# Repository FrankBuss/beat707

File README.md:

# Development environment

## Programmer and debug connection

For programming you can use an USBasp. The red wire of the USBasp programmer needs to be connected to the `pin 1` location:

For debugging, there is the jumper J5 near the MIDI connector, to connect a 5V UART receiver. Connect the top pin to GND (black wire in the image) and the bottom pin to the UART RX input (grey wire) :

## Fuse programming

The Arduino IDE doesn't flash the ATmega fuses, so initially you need to do this from the command line with avrdude like this:

```
avrdude -cusbasp -p m328 -B 10 -U lfuse:w:0xff:m
```
The output should look like this:

```
avrdude: set SCK frequency to 93750 Hz
avrdude: AVR device initialized and ready to accept instructions

Reading | ################################################## | 100% 0.00s

avrdude: Device signature = 0x1e9514 (probably m328)
avrdude: reading input file "0xff"
avrdude: writing lfuse (1 bytes):

Writing | ################################################## | 100% 0.00s

avrdude: 1 bytes of lfuse written
avrdude: verifying lfuse memory against 0xff:
avrdude: load data lfuse data from input file 0xff:
avrdude: input file 0xff contains 1 bytes
avrdude: reading on-chip lfuse data:

Reading | ################################################## | 100% 0.00s

avrdude: verifying ...
avrdude: 1 bytes of lfuse verified

avrdude: safemode: Fuses OK (E:FF, H:D9, L:FF)

avrdude done.  Thank you.
```

## Arduino IDE setup

First install the Arduino IDE. It was tested with Arduino 1.8.13. Then add the URL https://mcudude.github.io/MiniCore/package_MCUdude_MiniCore_index.json to "File->Preferences->Settings->Additional Board Manager URLs". Then you can install the new board with "Tools->Board->Boards Manager". Install "MiniCore by MCUdude", tested with version 2.1.0.

For programming you need an USBasp. You need to reduce the clock speed in the file `/home/username/bin/arduino-1.8.9/hardware/arduino/avr/programmers.txt`, where `username` is your username (on Linux, on Windows and Mac it might be different, see [here](https://www.arduino.cc/en/hacking/preferences)). Search for the `usbasp.program.extra_params` line and add the parameter `-B 10`. The full line now looks like this:

```
usbasp.program.extra_params=-Pusb -B 10
```

Restart the Arduino IDE after changing it.

After restart, select the new board: Tools->Board->MiniCore->ATmega328. For flashing the firmware, configure the following settings (Board, Clock, Variant and Bootloader needs to be changed):

Then select your programmer, for example USBasp:

After this you can program the ATmega328 on the board from the Arduino IDE by clicking on the right arrow.

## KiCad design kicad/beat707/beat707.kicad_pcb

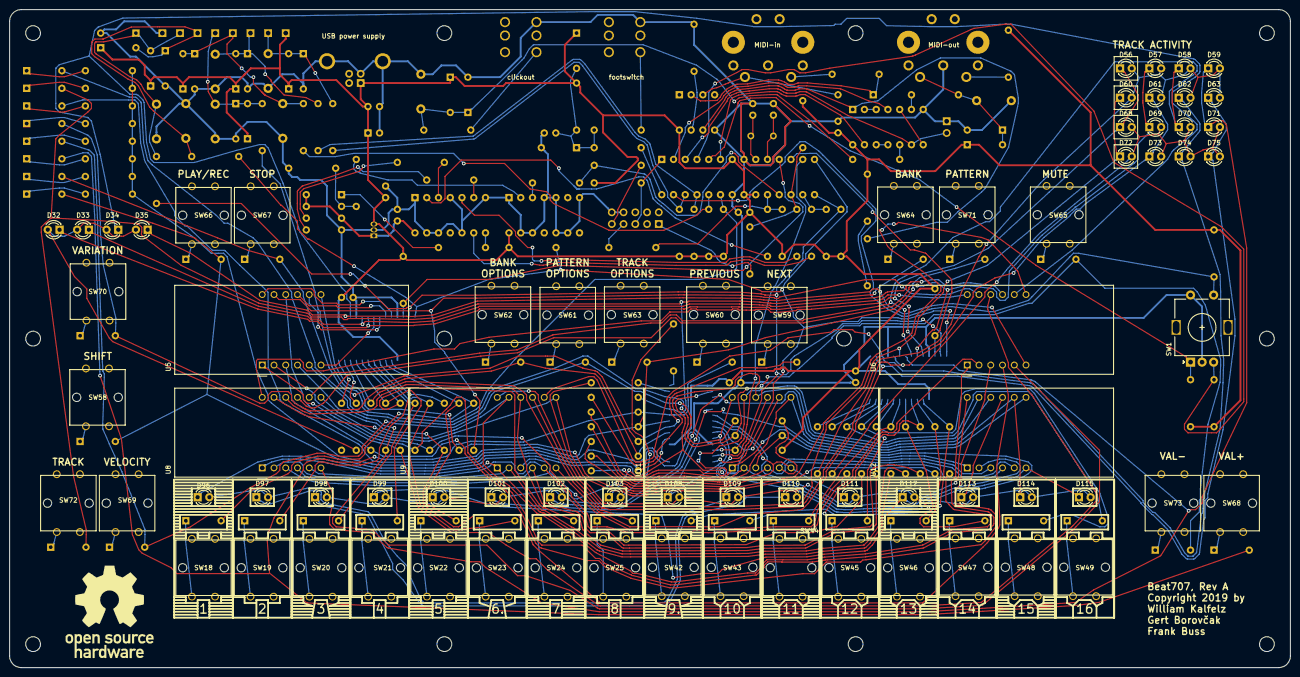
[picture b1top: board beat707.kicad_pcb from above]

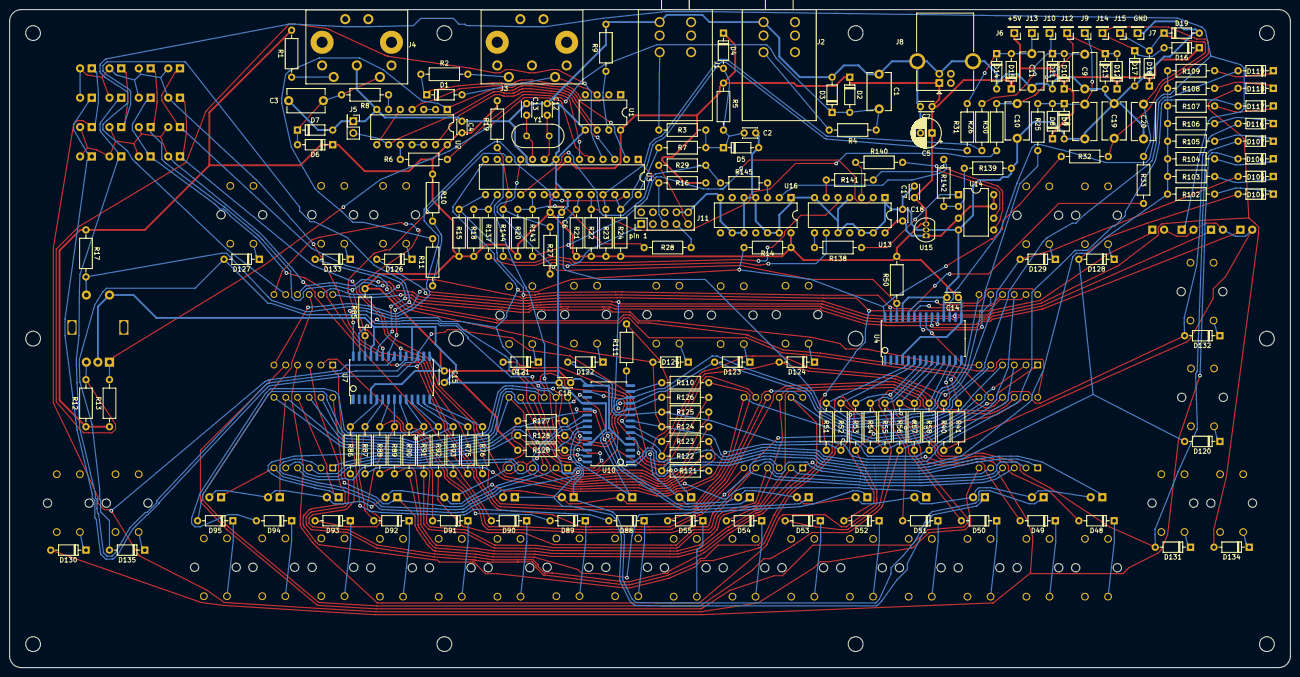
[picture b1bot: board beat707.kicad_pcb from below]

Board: 2 copper layers, 276.9 x 142.2 mm, 276 parts (188 on the bottom side), 188 nets.

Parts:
C1, C3, C8, C9, C10, C11, C19, C20: 1nF; C_Disc_D8.0mm_W5.0mm_P7.50mm
C2, C4, C6, C7, C14, C15, C16, C17, C18: 100nF; C_Disc_D3.0mm_W2.0mm_P2.50mm
C5: 47uF; CP_Radial_D6.3mm_P2.50mm
C12, C13: 22pF; C_Disc_D3.0mm_W2.0mm_P2.50mm
D1, D2, D3, D4, D5, D6, D7, D8, D9, D10, D11, D12, D13, D14, D15, D16, D17, D18, D19, D48, D49, D50, D51, D52, D53, D54, D55, D88, D89, D90, D91, D92, D93, D94, D95, D104, D105, D106, D107, D116, D117, D118, D119, D120, D121, D122, D123, D124, D125, D126, D127, D128, D129, D130, D131, D132, D133, D134, D135: 1N4148; D_DO-35_SOD27_P7.62mm_Horizontal
D32, D33, D34, D35, D56, D57, D58, D59, D60, D61, D62, D63, D68, D69, D70, D71, D72, D73, D74, D75, D96, D97, D98, D99, D100, D101, D102, D103, D108, D109, D110, D111, D112, D113, D114, D115: LED; LED_D3.0mm
H1, H2, H3, H4, H5, H6, H7, H8, H9, H10, H11, H12: MountingHole; MountingHole_3.2mm_M3
J1: footswitch; trs
J2: click-out; trs
J3: MIDI-in; din-5
J4: MIDI-out; din-5
J5: serial debug; PinHeader_2x01_P2.54mm_Vertical
J6: +5V; PinHeader_1x01_P2.54mm_Vertical
J7: GND; PinHeader_1x01_P2.54mm_Vertical
J8: USB_B; USB_B_OST_USB-B1HSxx_Horizontal
J9, J10, J12, J13, J14, J15: free IO; PinHeader_1x01_P2.54mm_Vertical
J11: ISP; PinHeader_2x05_P2.54mm_Vertical
LOGO1: Logo_Open_Hardware_Small; OSHW-Logo_19x20mm_SilkScreen
R1, R2, R3, R4, R6, R8, R10, R11, R25, R26, R30, R31, R32, R33, R40, R41, R75, R76, R110, R111: 220; R_Axial_DIN0207_L6.3mm_D2.5mm_P10.16mm_Horizontal
R5, R27, R28, R29: 1k; R_Axial_DIN0207_L6.3mm_D2.5mm_P10.16mm_Horizontal
R7, R9, R12, R13, R14, R15, R16, R17, R18, R19, R20, R21, R22, R23, R24, R50, R85, R120, R139: 10k; R_Axial_DIN0207_L6.3mm_D2.5mm_P10.16mm_Horizontal
R51, R52, R53, R54, R55, R56, R57, R58, R86, R87, R88, R89, R90, R91, R92, R93, R121, R122, R123, R124, R125, R126, R127, R128: 10; R_Axial_DIN0207_L6.3mm_D2.5mm_P10.16mm_Horizontal
R102, R103, R104, R105, R106, R107, R108, R109: 0; R_Axial_DIN0207_L6.3mm_D2.5mm_P10.16mm_Horizontal
R137, R138, R140, R141, R142, R143, R144, R145: 33; R_Axial_DIN0207_L6.3mm_D2.5mm_P10.16mm_Horizontal
SW1: Rotary_Encoder_Switch; RotaryEncoder_Alps_EC11E-Switch_Vertical_H20mm
SW18, SW19, SW20, SW21, SW22, SW23, SW24, SW25, SW42, SW43, SW44, SW45, SW46, SW47, SW48, SW49, SW58, SW59, SW60, SW61, SW62, SW63, SW64, SW65, SW66, SW67, SW68, SW69, SW70, SW71, SW72, SW73: SW_Push; B3F-through-hole
U1: 6N138; DIP-8_W7.62mm
U2: 74HC14; DIP-14_W7.62mm
U3: ATmega328-PU; DIP-28_W7.62mm
U4, U7, U10: TM1638; SOIC-28W_7.5x17.9mm_P1.27mm
U5, U6, U8, U9, U11, U12: CA56-12EWA
U13: SN74AHC125; DIP-14_W7.62mm
U14: MB85RS2MT; DIP-8_W7.62mm
U15: LP2950CZ-3.3G; TO-92_Inline
U16: SN74AHCT125; DIP-14_W7.62mm
Y1: 20 MHz; Crystal_HC49-U_Vertical

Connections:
+3V3: C18.2, U13.14, U14.3, U14.7, U14.8, U15.1
+5V: C4.1, C5.1, C6.1, C7.1, C14.1, C15.1, C16.1, C17.1, D2.1, D4.1, D6.1, D8.1, D10.1, D12.1, D14.1, D16.1, D18.1, J6.1, J8.1, R1.2, R5.2, R10.1, R12.1, R13.1, R14.2, R15.2, R16.1, R17.1, R18.2, R19.2, R20.2, R21.2, R22.2, R23.2, R24.2, R50.2, R85.2, R120.2, U1.8, U2.14, U3.7, U3.20, U3.21, U4.4, U4.15, U7.4, U7.15, U10.4, U10.15, U15.3, U16.14
/TM1638 Module/GRID1: U4.24, U5.12
/TM1638 Module/GRID2: U4.23, U5.9
/TM1638 Module/GRID3: U4.22, U5.8
/TM1638 Module/GRID4: U4.21, U5.6
/TM1638 Module/GRID5: D32.1, U4.20, U6.12
/TM1638 Module/GRID6: D33.1, U4.19, U6.9
/TM1638 Module/GRID7: D34.1, U4.17, U6.8
/TM1638 Module/GRID8: D35.1, U4.16, U6.6
/TM1638 Module/SEG1: D48.2, R51.2, U4.5
/TM1638 Module/SEG2: D52.2, R52.2, U4.6
/TM1638 Module/SEG3: D49.2, R53.2, U4.7
/TM1638 Module/SEG4: D53.2, R54.2, U4.8
/TM1638 Module/SEG5: D50.2, R55.2, U4.9
/TM1638 Module/SEG6: D54.2, R56.2, U4.10
/TM1638 Module/SEG7: D51.2, R57.2, U4.11
/TM1638 Module/SEG8: D55.2, R58.2, U4.12
/memory-module/CS: R18.1, R137.2, U3.16
/sheet5C6557AC/GRID1: D56.1, D68.1, U7.24, U8.12
/sheet5C6557AC/GRID2: D57.1, D69.1, U7.23, U8.9
/sheet5C6557AC/GRID3: D58.1, D70.1, U7.22, U8.8
/sheet5C6557AC/GRID4: D59.1, D71.1, U7.21, U8.6
/sheet5C6557AC/GRID5: D60.1, D72.1, U7.20, U9.12
/sheet5C6557AC/GRID6: D61.1, D73.1, U7.19, U9.9
/sheet5C6557AC/GRID7: D62.1, D74.1, U7.17, U9.8
/sheet5C6557AC/GRID8: D63.1, D75.1, U7.16, U9.6
/sheet5C6557AC/SEG1: D88.2, R86.2, U7.5
/sheet5C6557AC/SEG2: D92.2, R87.2, U7.6
/sheet5C6557AC/SEG3: D89.2, R88.2, U7.7
/sheet5C6557AC/SEG4: D93.2, R89.2, U7.8
/sheet5C6557AC/SEG5: D90.2, R90.2, U7.9
/sheet5C6557AC/SEG6: D94.2, R91.2, U7.10
/sheet5C6557AC/SEG7: D91.2, R92.2, U7.11
/sheet5C6557AC/SEG8: D95.2, R93.2, U7.12
/sheet5C6559D3/GRID1: D96.1, D108.1, U10.24, U11.12
/sheet5C6559D3/GRID2: D97.1, D109.1, U10.23, U11.9
/sheet5C6559D3/GRID3: D98.1, D110.1, U10.22, U11.8
/sheet5C6559D3/GRID4: D99.1, D111.1, U10.21, U11.6
/sheet5C6559D3/GRID5: D100.1, D112.1, U10.20, U12.12
/sheet5C6559D3/GRID6: D101.1, D113.1, U10.19, U12.9
/sheet5C6559D3/GRID7: D102.1, D114.1, U10.17, U12.8
/sheet5C6559D3/GRID8: D103.1, D115.1, U10.16, U12.6
/sheet5C6559D3/K1: R102.2, R103.2, R104.2, R105.2, R106.2, R107.2, R108.2, R109.2, U10.1
/sheet5C6559D3/SEG1: D104.2, D120.2, D128.2, R121.2, U10.5
/sheet5C6559D3/SEG2: D116.2, D124.2, D132.2, R122.2, U10.6
/sheet5C6559D3/SEG3: D105.2, D121.2, D129.2, R123.2, U10.7
/sheet5C6559D3/SEG4: D117.2, D125.2, D133.2, R124.2, U10.8
/sheet5C6559D3/SEG5: D106.2, D122.2, D130.2, R125.2, U10.9
/sheet5C6559D3/SEG6: D118.2, D126.2, D134.2, R126.2, U10.10
/sheet5C6559D3/SEG7: D107.2, D123.2, D131.2, R127.2, U10.11
/sheet5C6559D3/SEG8: D119.2, D127.2, D135.2, R128.2, U10.12
GND: C1.1, C2.1, C3.1, C4.2, C5.2, C6.2, C7.2, C8.1, C9.1, C10.1, C11.1, C12.1, C13.1, C14.2, C15.2, C16.2, C17.2, C18.1, C19.1, C20.1, D3.2, D5.2, D7.2, D9.2, D11.2, D13.2, D15.2, D17.2, D19.2, J1.S, J2.S, J4.2, J5.1, J7.1, J8.4, J8.5, J11.8, J11.10, R9.2, R139.1, SW1.C, SW1.S2, U1.5, U2.7, U3.8, U3.22, U4.18, U4.25, U7.18, U7.25, U10.18, U10.25, U13.1, U13.4, U13.7, U13.10, U13.12, U13.13, U14.4, U15.2, U16.1, U16.4, U16.5, U16.7, U16.9, U16.10, U16.12, U16.13
MIDI-in: U2.4, U3.2
MIDI-out: J5.2, U2.9, U3.3
MISO: R29.2, R145.1, U3.18
MOSI: R19.1, R27.2, R144.1, U3.17
unnamed: D32.2, D33.2, D34.2, D35.2, R40.2
unnamed: C1.2, D2.2, D3.1, R4.1, R6.2
unnamed: C2.2, D4.2, D5.1, R3.1, R5.1, R7.2
unnamed: C3.2, D6.2, D7.1, J4.5, R8.2
unnamed: C8.2, D8.2, D9.1, J9.1, R25.2
unnamed: C9.2, D10.2, D11.1, J10.1, R26.2
unnamed: C10.2, D12.2, D13.1, J12.1, R30.2
unnamed: C11.2, D14.2, D15.1, J13.1, R31.2
unnamed: C12.2, U3.9, Y1.2
unnamed: C13.2, U3.10, Y1.1
unnamed: C19.2, D16.2, D17.1, J14.1, R32.2
unnamed: C20.2, D18.2, D19.1, J15.1, R33.2
unnamed: D1.1, R2.1, U1.2
unnamed: D1.2, J3.5, U1.3
unnamed: D48.1, SW18.4
unnamed: D49.1, SW19.4
unnamed: D50.1, SW20.4
unnamed: D51.1, SW21.4
unnamed: D52.1, SW22.4
unnamed: D53.1, SW23.4
unnamed: D54.1, SW24.4
unnamed: D55.1, SW25.4
unnamed: D56.2, D57.2, D58.2, D59.2, D60.2, D61.2, D62.2, D63.2, R76.2
unnamed: D68.2, D69.2, D70.2, D71.2, D72.2, D73.2, D74.2, D75.2, R75.2
unnamed: D88.1, SW42.4
unnamed: D89.1, SW43.4
unnamed: D90.1, SW44.4
unnamed: D91.1, SW45.4
unnamed: D92.1, SW46.4
unnamed: D93.1, SW47.4
unnamed: D94.1, SW48.4
unnamed: D95.1, SW49.4
unnamed: D96.2, D97.2, D98.2, D99.2, D100.2, D101.2, D102.2, D103.2, R111.2
unnamed: D104.1, R102.1
unnamed: D105.1, R103.1
unnamed: D106.1, R104.1
unnamed: D107.1, R105.1
unnamed: D108.2, D109.2, D110.2, D111.2, D112.2, D113.2, D114.2, D115.2, R110.2
unnamed: D116.1, R106.1
unnamed: D117.1, R107.1
unnamed: D118.1, R108.1
unnamed: D119.1, R109.1
unnamed: D120.1, SW58.4
unnamed: D121.1, SW59.4
unnamed: D122.1, SW60.4
unnamed: D123.1, SW61.4
unnamed: D124.1, SW62.4
unnamed: D125.1, SW63.4
unnamed: D126.1, SW64.4
unnamed: D127.1, SW65.4
unnamed: D128.1, SW66.4
unnamed: D129.1, SW67.4
unnamed: D130.1, SW68.4
unnamed: D131.1, SW69.4
unnamed: D132.1, SW70.4
unnamed: D133.1, SW71.4
unnamed: D134.1, SW72.4
unnamed: D135.1, SW73.4
unnamed: J1.T, R3.2
unnamed: J2.T, R4.2
unnamed: J3.4, R2.2
unnamed: J4.4, R1.1
unnamed: J11.1, R27.1
unnamed: J11.7, R28.1
unnamed: J11.9, R29.1
unnamed: R6.1, U2.10
unnamed: R8.1, U2.6
unnamed: R9.1, U1.7
unnamed: R10.2, R11.1
unnamed: R11.2, U1.6, U2.1
unnamed: R12.2, SW1.B, U3.4
unnamed: R13.2, SW1.A, U3.5
unnamed: R17.2, SW1.S1, U3.27
unnamed: R21.1, R25.1, U3.23
unnamed: R22.1, R30.1, U3.24
unnamed: R23.1, R26.1, U3.25
unnamed: R24.1, R31.1, U3.26
unnamed: R40.1, U4.13
unnamed: R41.1, U4.14
unnamed: R51.1, U5.11, U6.11
unnamed: R52.1, U5.7, U6.7
unnamed: R53.1, U5.4, U6.4
unnamed: R54.1, U5.2, U6.2
unnamed: R55.1, U5.1, U6.1
unnamed: R56.1, U5.10, U6.10
unnamed: R57.1, U5.5, U6.5
unnamed: R58.1, U5.3, U6.3
unnamed: R75.1, U7.13
unnamed: R76.1, U7.14
unnamed: R86.1, U8.11, U9.11
unnamed: R87.1, U8.7, U9.7
unnamed: R88.1, U8.4, U9.4
unnamed: R89.1, U8.2, U9.2
unnamed: R90.1, U8.1, U9.1
unnamed: R91.1, U8.10, U9.10
unnamed: R92.1, U8.5, U9.5
unnamed: R93.1, U8.3, U9.3
unnamed: R110.1, U10.13
unnamed: R111.1, U10.14
unnamed: R121.1, U11.11, U12.11
unnamed: R122.1, U11.7, U12.7
unnamed: R123.1, U11.4, U12.4
unnamed: R124.1, U11.2, U12.2
unnamed: R125.1, U11.1, U12.1
unnamed: R126.1, U11.10, U12.10
unnamed: R127.1, U11.5, U12.5
unnamed: R128.1, U11.3, U12.3
unnamed: R137.1, U13.9
unnamed: R138.1, U14.1
unnamed: R138.2, U13.8
unnamed: R139.2, R142.2, U14.2
unnamed: R140.1, U13.3
unnamed: R140.2, U14.6
unnamed: R141.1, U13.6
unnamed: R141.2, U14.5
unnamed: R142.1, U16.2
unnamed: R143.2, U13.2
unnamed: R144.2, U13.5
unnamed: R145.2, U16.3
unnamed: U2.2, U2.3
unnamed: U2.5, U2.8
unnamed: U2.11, U2.12
RESET: J11.5, R16.2, U3.1
SCK: R20.1, R28.2, R143.1, U3.19
click-out: U2.13, U3.6
footswitch: R7.1, U3.28
tm1638-clk: R15.1, R33.1, U3.15, U4.27, U7.27, U10.27
tm1638-dio-1: R50.1, U3.11, U4.26
tm1638-dio-2: R85.1, U3.12, U7.26
tm1638-dio-3: R120.1, U3.13, U10.26
tm1638-stb: R14.1, R32.1, U3.14, U4.28, U7.28, U10.28

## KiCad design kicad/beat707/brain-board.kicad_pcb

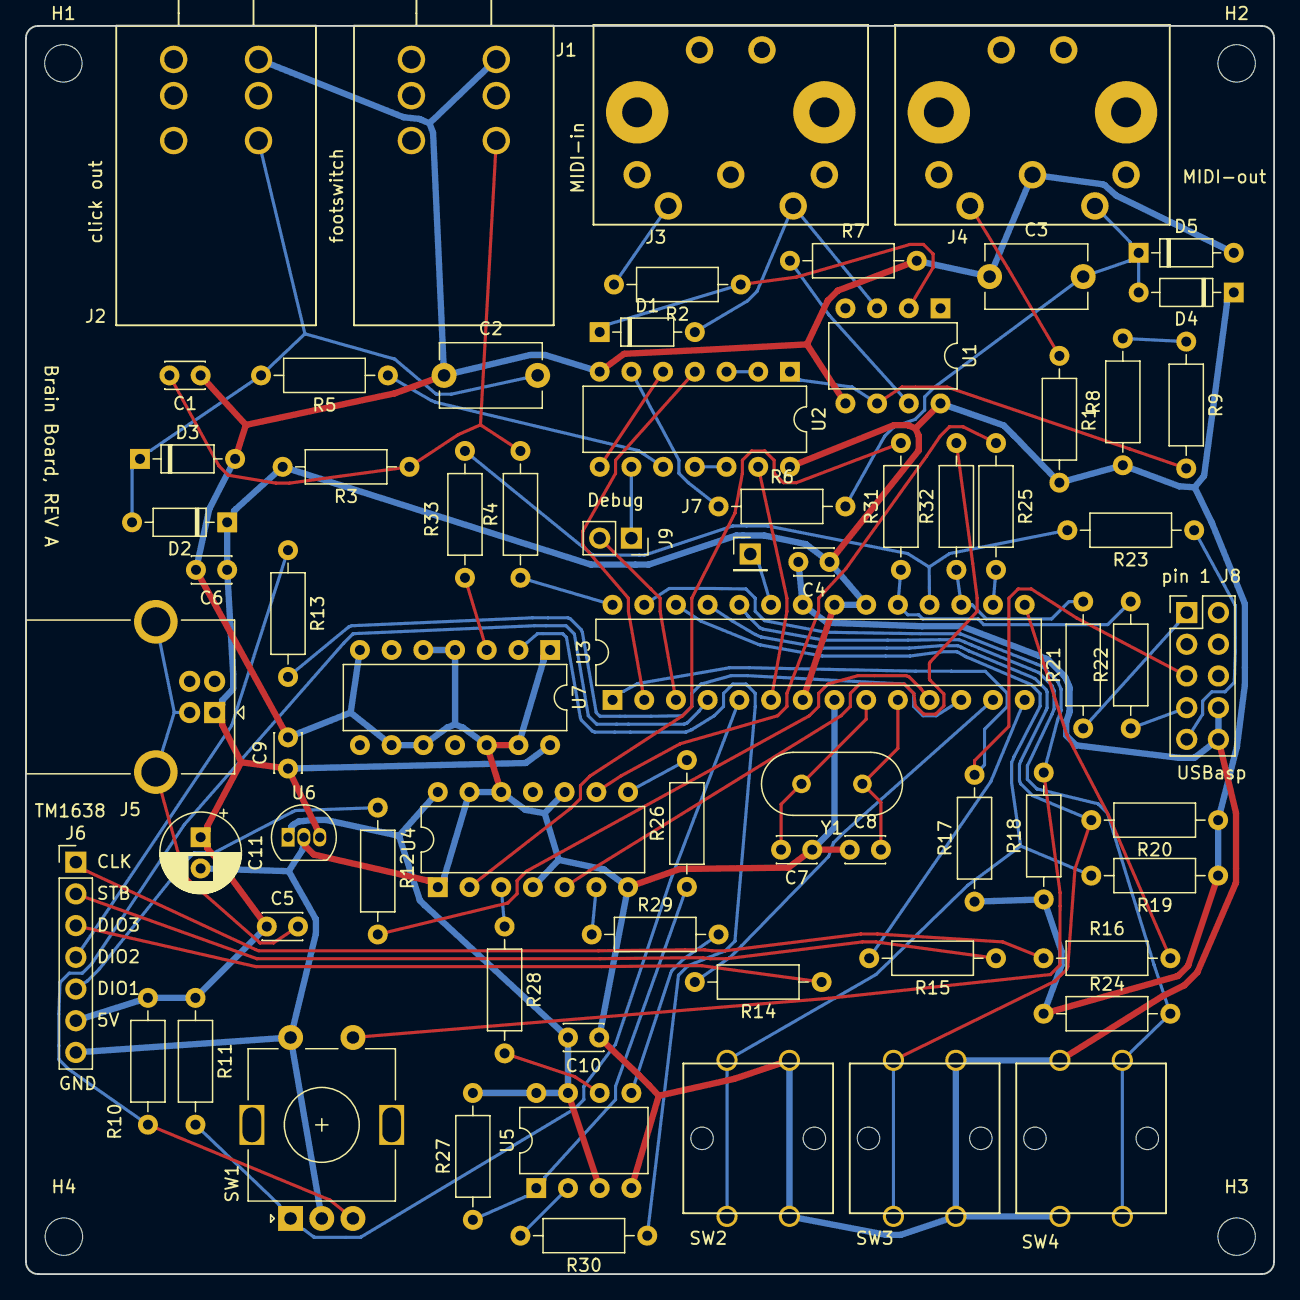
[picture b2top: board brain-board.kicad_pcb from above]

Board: 2 copper layers, 100.0 x 100.0 mm, 74 parts (0 on the bottom side), 63 nets.

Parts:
C1, C4, C5, C6, C9, C10: 100nF; C_Disc_D3.0mm_W2.0mm_P2.50mm
C2, C3: 1nF; C_Disc_D8.0mm_W5.0mm_P7.50mm
C7, C8: 22pF; C_Disc_D3.0mm_W2.0mm_P2.50mm
C11: 10uF; CP_Radial_D6.3mm_P2.50mm
D1, D2, D3, D4, D5: 1N4148; D_DO-35_SOD27_P7.62mm_Horizontal
H1, H2, H3, H4: MountingHole; MountingHole_3mm
J1: footswitch; trs
J2: click-out; trs
J3: MIDI-in; din-5
J4: MIDI-out; din-5
J5: USB_B; USB_B_OST_USB-B1HSxx_Horizontal
J6: Conn_01x07; PinHeader_1x07_P2.54mm_Vertical
J7: free IO; PinHeader_1x01_P2.54mm_Vertical
J8: ISP; PinHeader_2x05_P2.54mm_Vertical
J9: Conn_01x02_Male; PinSocket_1x02_P2.54mm_Vertical
R1, R2, R5, R6, R8, R9: 220; R_Axial_DIN0207_L6.3mm_D2.5mm_P10.16mm_Horizontal
R3, R21, R22, R23: 1k; R_Axial_DIN0207_L6.3mm_D2.5mm_P10.16mm_Horizontal
R4, R7, R10, R11, R17, R18, R19, R20, R24, R27: 10k; R_Axial_DIN0207_L6.3mm_D2.5mm_P10.16mm_Horizontal
R12, R13, R14, R15, R16, R25, R26, R28, R29, R30, R31, R32, R33: 33; R_Axial_DIN0207_L6.3mm_D2.5mm_P10.16mm_Horizontal
SW1: Rotary_Encoder_Switch; RotaryEncoder_Alps_EC11E-Switch_Vertical_H20mm
SW2, SW3, SW4: SW_Push; B3F-through-hole
U1: 6N138; DIP-8_W7.62mm
U2: 74HC14; DIP-14_W7.62mm
U3: ATmega328-PU; DIP-28_W7.62mm
U4: SN74AHC125; DIP-14_W7.62mm
U5: MB85RS2MT; DIP-8_W7.62mm
U6: LP2950CZ-3.3G; TO-92_Inline
U7: SN74AHCT125; DIP-14_W7.62mm
Y1: 20 MHz; Crystal_HC49-U_Vertical

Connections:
+3V3: C10.2, R27.2, U4.14, U5.3, U5.7, U5.8, U6.1
+5V: C4.1, C5.1, C6.1, C9.1, C11.1, D2.1, D4.1, J5.1, J6.6, R1.2, R3.2, R8.1, R10.1, R11.1, R17.1, R18.1, R19.1, R20.1, R24.1, U1.8, U2.14, U3.7, U3.20, U3.21, U6.3, U7.14
/memory-module/CS: R25.2, U3.16
GND: C1.1, C2.1, C3.1, C4.2, C6.2, C7.1, C8.1, C9.2, C10.1, C11.2, D3.2, D5.2, J1.S, J2.S, J4.2, J6.7, J8.8, J8.10, R7.2, SW1.C, SW1.S2, SW2.3, SW2.4, SW3.3, SW3.4, SW4.3, SW4.4, U1.5, U2.7, U3.8, U3.22, U4.1, U4.4, U4.7, U4.10, U4.12, U4.13, U5.4, U6.2, U7.1, U7.4, U7.5, U7.7, U7.9, U7.10, U7.12, U7.13
MIDI-in: U2.4, U3.2
MIDI-out: J9.2, U3.3
MISO: R23.2, R33.1, U3.18
MOSI: R21.2, R32.1, U3.17
unnamed: C1.2, J1.T, R3.1, R4.2
unnamed: C2.2, D2.2, D3.1, J2.T, R5.2
unnamed: C3.2, D4.2, D5.1, J4.5, R6.2
unnamed: C5.2, J5.4, J5.5
unnamed: C7.2, U3.9, Y1.2
unnamed: C8.2, U3.10, Y1.1
unnamed: D1.1, R2.1, U1.2
unnamed: D1.2, J3.5, U1.3
unnamed: J3.4, R2.2
unnamed: J4.4, R1.1
unnamed: J7.1, U3.23
unnamed: J8.1, R21.1
unnamed: J8.7, R22.1
unnamed: J8.9, R23.1
unnamed: J9.1, U2.9
unnamed: R5.1, U2.10
unnamed: R6.1, U2.6
unnamed: R7.1, U1.7
unnamed: R8.2, R9.1
unnamed: R9.2, U1.6, U2.1
unnamed: R10.2, SW1.B, U3.4
unnamed: R11.2, SW1.A, U3.5
unnamed: R12.2, U3.11
unnamed: R13.2, U3.12
unnamed: R14.2, U3.13
unnamed: R15.2, U3.14
unnamed: R16.2, U3.15
unnamed: R18.2, SW1.S1, U3.27
unnamed: R19.2, SW2.1, SW2.2, U3.26
unnamed: R20.2, SW3.1, SW3.2, U3.25
unnamed: R24.2, SW4.1, SW4.2, U3.24
unnamed: R25.1, U4.9
unnamed: R26.1, R27.1, U5.1
unnamed: R26.2, U4.8
unnamed: R28.1, U4.3
unnamed: R28.2, U5.6
unnamed: R29.1, U4.6
unnamed: R29.2, U5.5
unnamed: R30.1, U7.2
unnamed: R30.2, U5.2
unnamed: R31.2, U4.2
unnamed: R32.2, U4.5
unnamed: R33.2, U7.3
unnamed: U2.2, U2.3
unnamed: U2.5, U2.8
unnamed: U2.11, U2.12
RESET: J8.5, R17.2, U3.1
SCK: R22.2, R31.1, U3.19
click-out: U2.13, U3.6
footswitch: R4.1, U3.28
tm1638-clk: J6.1, R16.1
tm1638-dio-1: J6.5, R12.1
tm1638-dio-2: J6.4, R13.1
tm1638-dio-3: J6.3, R14.1
tm1638-stb: J6.2, R15.1

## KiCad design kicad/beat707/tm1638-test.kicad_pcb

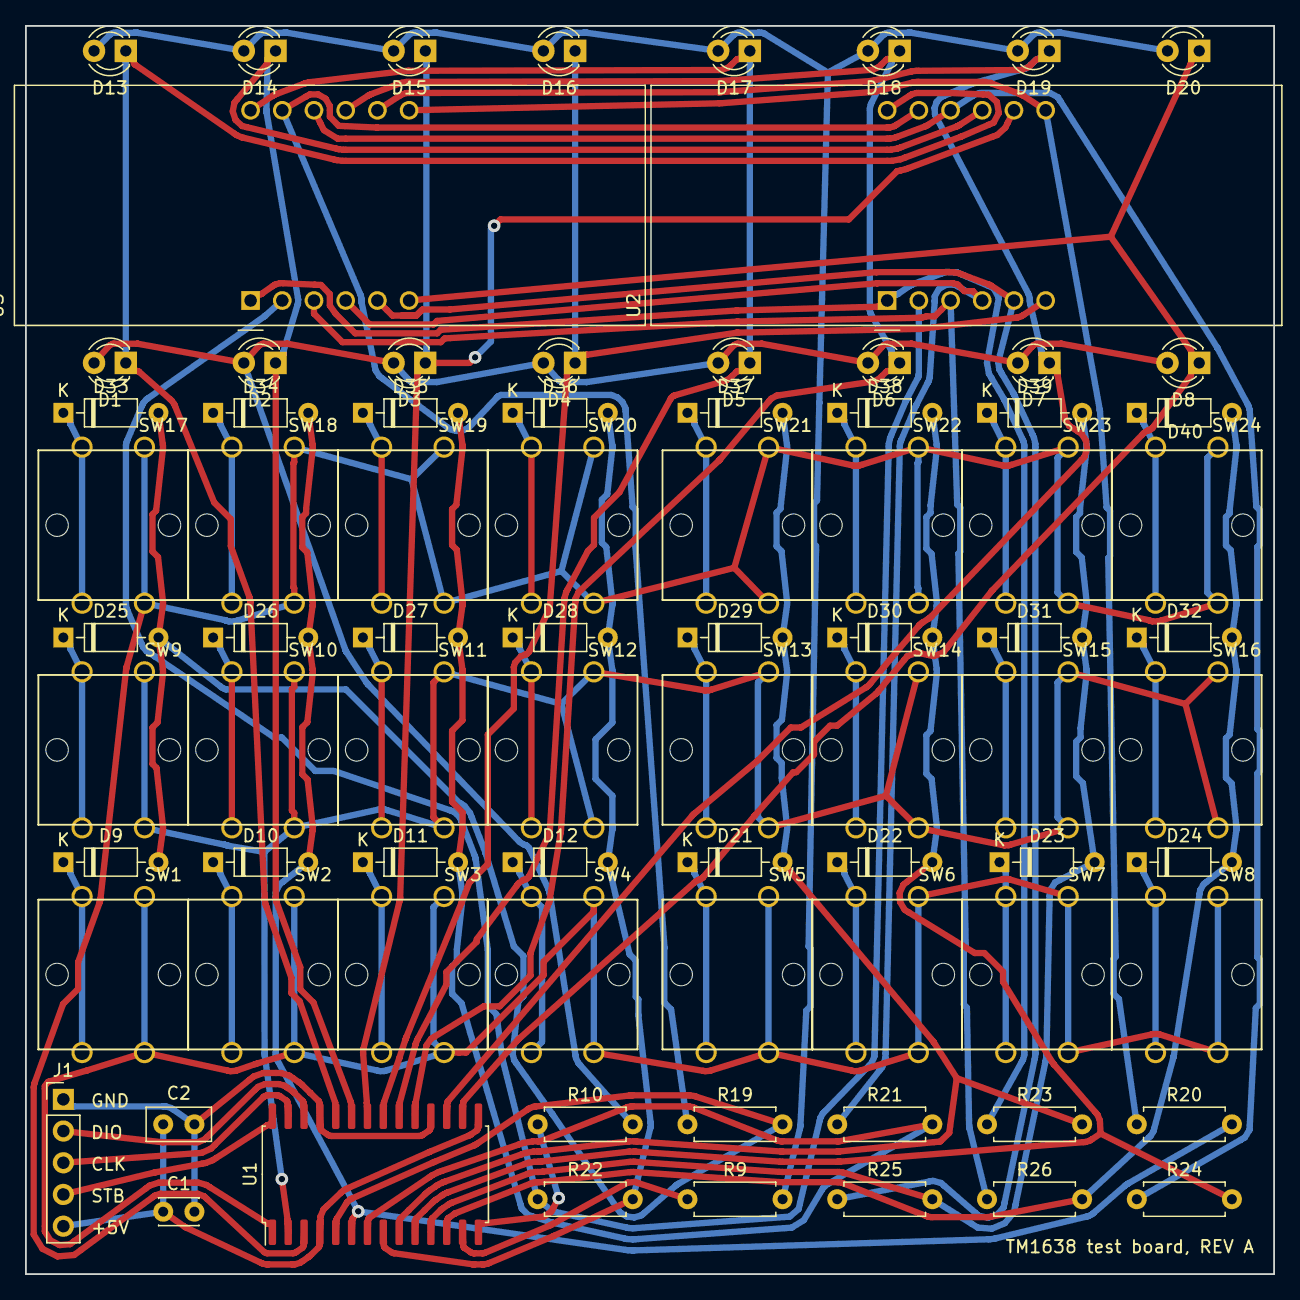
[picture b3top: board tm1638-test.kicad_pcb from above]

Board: 2 copper layers, 100.0 x 100.0 mm, 80 parts (0 on the bottom side), 60 nets.

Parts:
C1: 100nF; C_Disc_D3.0mm_W2.0mm_P2.50mm
C2: 10uF; C_Disc_D5.0mm_W2.5mm_P2.50mm
D1, D2, D3, D4, D5, D6, D7, D8, D13, D14, D15, D16, D17, D18, D19, D20: LED; LED_D3.0mm
D9, D10, D11, D12, D21, D22, D23, D24, D25, D26, D27, D28, D29, D30, D31, D32, D33, D34, D35, D36, D37, D38, D39, D40: 1N4148; D_DO-35_SOD27_P7.62mm_Horizontal
J1: Conn_01x05_Male; PinHeader_1x05_P2.54mm_Vertical
R9, R10, R19, R20, R21, R22, R23, R24, R25, R26: 51; R_Axial_DIN0207_L6.3mm_D2.5mm_P7.62mm_Horizontal
SW1, SW2, SW3, SW4, SW5, SW6, SW7, SW8, SW9, SW10, SW11, SW12, SW13, SW14, SW15, SW16, SW17, SW18, SW19, SW20, SW21, SW22, SW23, SW24: SW_Push; B3F-through-hole
U1: TM1638; SOIC-28W_7.5x17.9mm_P1.27mm
U2, U3: CA56-12EWA

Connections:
+5V: C1.1, C2.1, J1.5, U1.4, U1.15
/TM1638 Module/CLK: J1.3, U1.27
/TM1638 Module/DIO: J1.2, U1.26
/TM1638 Module/GRID1: D1.1, D13.1, U1.24, U2.12
/TM1638 Module/GRID2: D2.1, D14.1, U1.23, U2.9
/TM1638 Module/GRID3: D3.1, D15.1, U1.22, U2.8
/TM1638 Module/GRID4: D4.1, D16.1, U1.21, U2.6
/TM1638 Module/GRID5: D5.1, D17.1, U1.20, U3.12
/TM1638 Module/GRID6: D6.1, D18.1, U1.19, U3.9
/TM1638 Module/GRID7: D7.1, D19.1, U1.17, U3.8
/TM1638 Module/GRID8: D8.1, D20.1, U1.16, U3.6
/TM1638 Module/K1: SW1.1, SW1.2, SW2.1, SW2.2, SW3.1, SW3.2, SW4.1, SW4.2, SW5.1, SW5.2, SW6.1, SW6.2, SW7.1, SW7.2, SW8.1, SW8.2, U1.1
/TM1638 Module/K2: SW9.1, SW9.2, SW10.1, SW10.2, SW11.1, SW11.2, SW12.1, SW12.2, SW13.1, SW13.2, SW14.1, SW14.2, SW15.1, SW15.2, SW16.1, SW16.2, U1.2
/TM1638 Module/K3: SW17.1, SW17.2, SW18.1, SW18.2, SW19.1, SW19.2, SW20.1, SW20.2, SW21.1, SW21.2, SW22.1, SW22.2, SW23.1, SW23.2, SW24.1, SW24.2, U1.3
/TM1638 Module/SEG1: D9.2, D25.2, D33.2, R19.2, U1.5
/TM1638 Module/SEG2: D10.2, D26.2, D34.2, R20.2, U1.6
/TM1638 Module/SEG3: D11.2, D27.2, D35.2, R21.2, U1.7
/TM1638 Module/SEG4: D12.2, D28.2, D36.2, R22.2, U1.8
/TM1638 Module/SEG5: D21.2, D29.2, D37.2, R23.2, U1.9
/TM1638 Module/SEG6: D22.2, D30.2, D38.2, R24.2, U1.10
/TM1638 Module/SEG7: D23.2, D31.2, D39.2, R25.2, U1.11
/TM1638 Module/SEG8: D24.2, D32.2, D40.2, R26.2, U1.12
/TM1638 Module/STB: J1.4, U1.28
GND: C1.2, C2.2, J1.1, U1.18, U1.25
unnamed: D1.2, D2.2, D3.2, D4.2, D5.2, D6.2, D7.2, D8.2, R10.2
unnamed: D9.1, SW1.3, SW1.4
unnamed: D10.1, SW2.3, SW2.4
unnamed: D11.1, SW3.3, SW3.4
unnamed: D12.1, SW4.3, SW4.4
unnamed: D13.2, D14.2, D15.2, D16.2, D17.2, D18.2, D19.2, D20.2, R9.2
unnamed: D21.1, SW5.3, SW5.4
unnamed: D22.1, SW6.3, SW6.4
unnamed: D23.1, SW7.3, SW7.4
unnamed: D24.1, SW8.3, SW8.4
unnamed: D25.1, SW9.3, SW9.4
unnamed: D26.1, SW10.3, SW10.4
unnamed: D27.1, SW11.3, SW11.4
unnamed: D28.1, SW12.3, SW12.4
unnamed: D29.1, SW13.3, SW13.4
unnamed: D30.1, SW14.3, SW14.4
unnamed: D31.1, SW15.3, SW15.4
unnamed: D32.1, SW16.3, SW16.4
unnamed: D33.1, SW17.3, SW17.4
unnamed: D34.1, SW18.3, SW18.4
unnamed: D35.1, SW19.3, SW19.4
unnamed: D36.1, SW20.3, SW20.4
unnamed: D37.1, SW21.3, SW21.4
unnamed: D38.1, SW22.3, SW22.4
unnamed: D39.1, SW23.3, SW23.4
unnamed: D40.1, SW24.3, SW24.4
unnamed: R9.1, U1.13
unnamed: R10.1, U1.14
unnamed: R19.1, U2.11, U3.11
unnamed: R20.1, U2.7, U3.7
unnamed: R21.1, U2.4, U3.4
unnamed: R22.1, U2.2, U3.2
unnamed: R23.1, U2.1, U3.1
unnamed: R24.1, U2.10, U3.10
unnamed: R25.1, U2.5, U3.5
unnamed: R26.1, U2.3, U3.3

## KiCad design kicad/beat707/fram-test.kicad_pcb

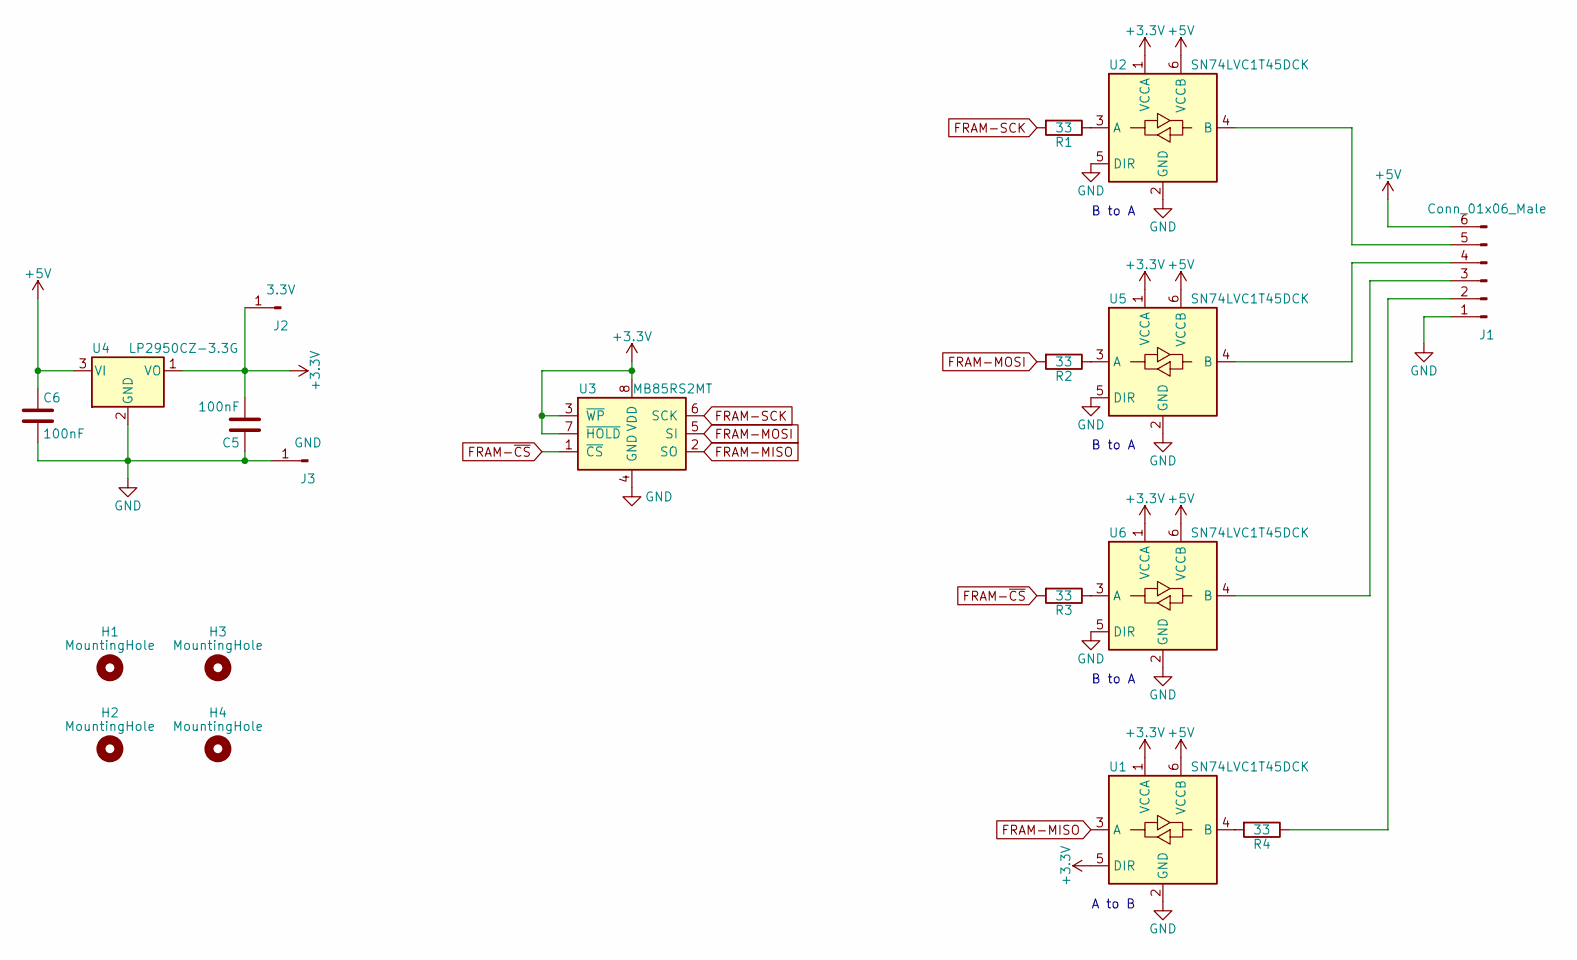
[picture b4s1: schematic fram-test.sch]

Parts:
C5, C6: 100nF; C_Disc_D3.0mm_W2.0mm_P2.50mm
H1, H2, H3, H4: MountingHole; MountingHole_2.2mm_M2
J1: Conn_01x06_Male; PinHeader_1x06_P2.54mm_Vertical
J2: 3.3V; PinHeader_1x01_P2.54mm_Vertical
J3: GND; PinHeader_1x01_P2.54mm_Vertical
R1, R2, R3, R4: 33; R_Axial_DIN0207_L6.3mm_D2.5mm_P10.16mm_Horizontal
U1, U2, U5, U6: SN74LVC1T45DCK; SOT-363_SC-70-6
U3: MB85RS2MT; DIP-8_W7.62mm
U4: LP2950CZ-3.3G; TO-92_Inline

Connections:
+3V3: C5.2, J2.1, U1.1 (VCCA), U1.5 (DIR), U2.1 (VCCA), U3.3 (~WP), U3.7 (~HOLD), U3.8 (VDD), U4.1 (VO), U5.1 (VCCA), U6.1 (VCCA)
+5V: C6.1, J1.6, U1.6 (VCCB), U2.6 (VCCB), U4.3 (VI), U5.6 (VCCB), U6.6 (VCCB)
FRAM-MISO: U1.3 (A), U3.2 (SO)
FRAM-MOSI: R2.2, U3.5 (SI)
FRAM-SCK: R1.2, U3.6 (SCK)
FRAM-~CS: R3.2, U3.1 (~CS)
GND: C5.1, C6.2, J1.1, J3.1, U1.2 (GND), U2.2 (GND), U2.5 (DIR), U3.4 (GND), U4.2 (GND), U5.2 (GND), U5.5 (DIR), U6.2 (GND), U6.5 (DIR)
unnamed: J1.2, R4.1
unnamed: J1.3, U6.4 (B)
unnamed: J1.4, U5.4 (B)
unnamed: J1.5, U2.4 (B)
unnamed: R1.1, U2.3 (A)
unnamed: R2.1, U5.3 (A)
unnamed: R3.1, U6.3 (A)
unnamed: R4.2, U1.4 (B)

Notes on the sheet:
A to B
B to A

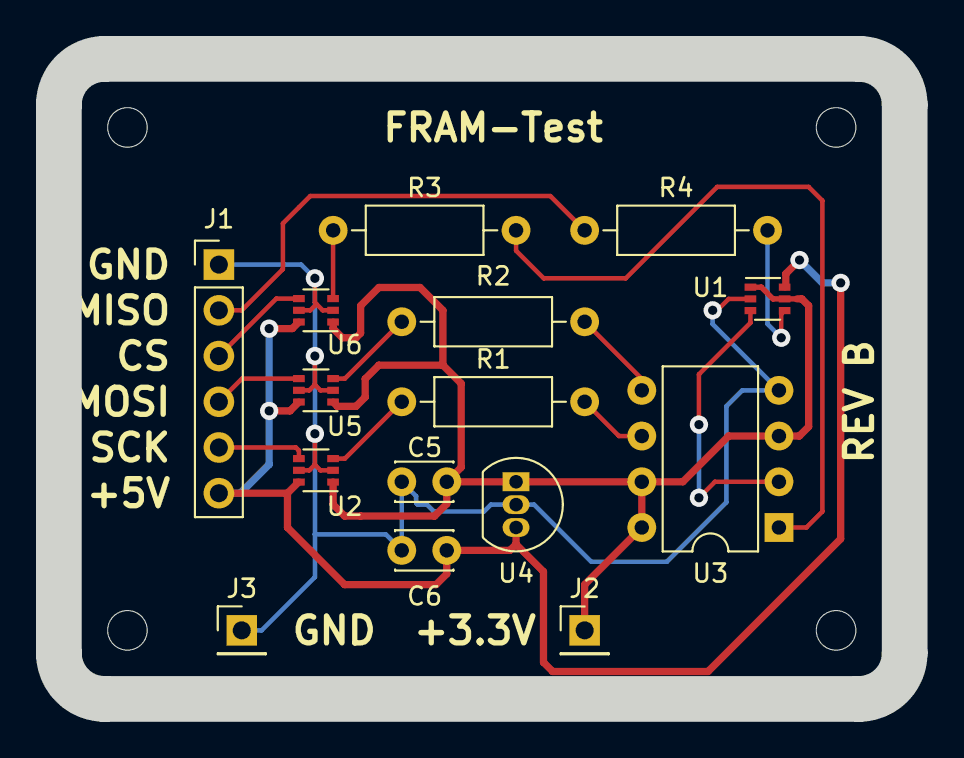
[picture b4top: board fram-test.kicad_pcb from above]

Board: 2 copper layers, 47.0 x 35.6 mm, 19 parts (0 on the bottom side), 15 nets.

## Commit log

2019-02-15 Initial Arduino Source Code
    The last code been used, with the addition of Pulse Click Out
2019-02-23 additional buttons and new layout for beatNXT 2.0
2019-02-24 3 new buttons and a rotary encoder (ALPS EC12E)
2019-02-24 all LEDs changed to through-hole, 3mm
2019-02-25 Create beat707_layout25Feb.kicad_pcb
    unfinished kicad design. still trying with the layout, finding best position for left/right hand.
2019-02-25 new version from Gert with changed positions
2019-02-26 final UI layout
    silkscreen still missing, boardsize too large, spacing on bottom and left edge should be sufficient as guide for final board size
2019-02-26 final UI layout +silkscreen
    basic silkscreen, more to come
2019-02-26 deleted
2019-03-07 more LEDs, switches and resistors for version encoding
2019-03-15 test board for TM1638 and main board finished
2019-03-15 board updated and schematic cleanup
2019-03-16 placed switches+leds, unfinished
2019-03-18 components on pcb sorted, not needed = below
2019-03-19 removed unneded files
2019-03-19 3D model for button
2019-03-19 making brainboard space
    mute leds moved to 4x4 block upper right (will change leds to come from right side tm1638 for easier routing), added spaces between 4 steps, TM1638 part placement = just a try, brainboard parts not p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
2019-03-20 Update beat707.kicad_pcb
    semi final UI element placement & board size. missing: optional mounting holes (square footprint)
2019-03-25 Update beat707.kicad_pcb
    first try for step silkscreen
2019-03-25 restored deleted files and added all 3D models
2019-04-06 new FRAM test and TM!638 board cleanups
2019-04-10 Added 1 Pattern Mode
    Changes by WilliamK
2019-04-11 Updated MIDI Output Buffer
    Improved the midi buffer output, using a faster code so notes are output faster. The code buffers the next tick of the sequencer ahead of time, so when the time comes to output the notes everything i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
2019-04-11 MIDI Echo Fixed
    Fixed the MIDI Input Echo code so it doesn't conflicts with the sequencer interrupt. Before I start sending the note echo I set a variable that tells the sequencer interrupt to perform after I finish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
2019-04-11 Added Version Number 0001
2019-04-12 V0002
    - Removed some stuff from the interface that is pattern/bank related.
    - Added Track Len to the global menu. Goes from 1 to 16. It will follow the Variations ABCD but crop the track length using the LEN value instead. Default is 16, the whole track (all steps).
2019-04-13 V004 (added EEPROM support)
    - Added Program Change (PC) Offset to the Global Menu, with two values: starting at 0 or starting at 1. This is set per track.
    - Added Save to Internal EEPROM (uses the ATmega328 EEPROM) for all data. It compress the pattern steps to fit things out. Here I used a very simple and fast compression code. It checks for zeros in 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
2019-04-13 Added Memory Usage Chart
2019-04-14 new voltage level translation and ISP header
2019-04-14 FRAM test board deleted, because already tested on breadboard
2019-05-04 brain board added, bufixes and final board synchronized with schematic
2019-05-04 mounting holes and all parts placed
2019-05-04 mounting holes
2019-05-05 5 new menu buttons
2019-05-08 new documentation and minor circuit changes
2019-05-08 debug pin
2019-05-08 test code for the brainboard
2019-06-06 final component placement and routing
2019-06-14 final routed version
2021-01-17 Panel for snijlab.nl
2021-02-27 changes for new KiCad version, added panel file, and added documentation
2021-02-28 interactive BOM
2023-04-21 vcvrack simulation, initial commit
2023-04-29 initial port of the Arduino code to C++
2023-04-29 added LCD display simulation
2023-04-30 buttons added
2023-05-07 added flash emulation and fixed buttons
2023-05-15 fixed flash and keyboard read speed

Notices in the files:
kicad/beat707/beat707.kicad_pcb:
Copyright 2019 by
William Kalfelz
